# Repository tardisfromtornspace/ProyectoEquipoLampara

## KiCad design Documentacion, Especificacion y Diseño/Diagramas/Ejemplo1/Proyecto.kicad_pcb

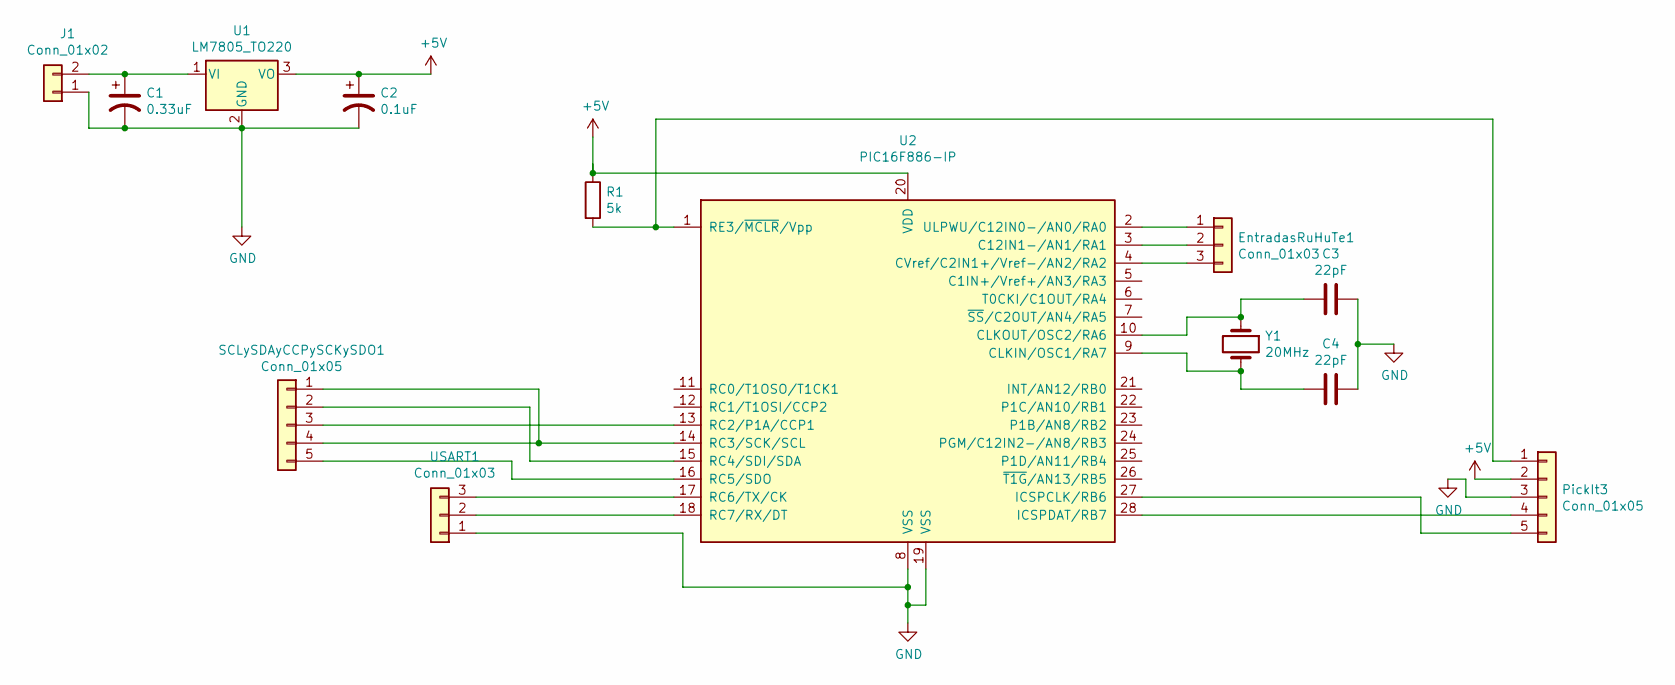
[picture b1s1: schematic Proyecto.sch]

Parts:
C1: 0.33uF; CP_Radial_D5.0mm_P2.50mm
C2: 0.1uF; CP_Radial_D5.0mm_P2.50mm
C3, C4: 22pF; C_Disc_D5.0mm_W2.5mm_P2.50mm
EntradasRuHuTe1: Conn_01x03; PinHeader_1x03_P2.54mm_Vertical
J1: Conn_01x02; TerminalBlock_bornier-2_P5.08mm
PickIt3: Conn_01x05; PinHeader_1x05_P2.54mm_Vertical
R1: 5k; R_Axial_DIN0204_L3.6mm_D1.6mm_P7.62mm_Horizontal
SCLySDAyCCPySCKySDO1: Conn_01x05; PinHeader_1x05_P2.54mm_Vertical
U1: LM7805_TO220; TO-220-3_Vertical
U2: PIC16F886-IP; DIP-28_W7.62mm_LongPads
USART1: Conn_01x03; PinHeader_1x03_P2.54mm_Vertical
Y1: 20MHz; Crystal_HC18-U_Vertical

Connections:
+5V: C2.1, PickIt3.2, R1.1, U1.3 (VO), U2.20 (VDD)
GND: C1.2, C2.2, C3.1, C4.1, J1.1, PickIt3.3, U1.2 (GND), U2.8 (VSS), U2.19 (VSS), USART1.1
unnamed: C1.1, J1.2, U1.1 (VI)
unnamed: C3.2, U2.10 (CLKOUT/OSC2/RA6), Y1.1
unnamed: C4.2, U2.9 (CLKIN/OSC1/RA7), Y1.2
unnamed: EntradasRuHuTe1.1, U2.2 (ULPWU/C12IN0-/AN0/RA0)
unnamed: EntradasRuHuTe1.2, U2.3 (C12IN1-/AN1/RA1)
unnamed: EntradasRuHuTe1.3, U2.4 (CVref/C2IN1+/Vref-/AN2/RA2)
unnamed: PickIt3.1, R1.2, U2.1 (RE3/~MCLR~/Vpp)
unnamed: PickIt3.4, U2.28 (ICSPDAT/RB7)
unnamed: PickIt3.5, U2.27 (ICSPCLK/RB6)
unnamed: SCLySDAyCCPySCKySDO1.1, SCLySDAyCCPySCKySDO1.4, U2.14 (RC3/SCK/SCL)
unnamed: SCLySDAyCCPySCKySDO1.2, U2.15 (RC4/SDI/SDA)
unnamed: SCLySDAyCCPySCKySDO1.3, U2.13 (RC2/P1A/CCP1)
unnamed: SCLySDAyCCPySCKySDO1.5, U2.16 (RC5/SDO)
unnamed: U2.17 (RC6/TX/CK), USART1.3
unnamed: U2.18 (RC7/RX/DT), USART1.2

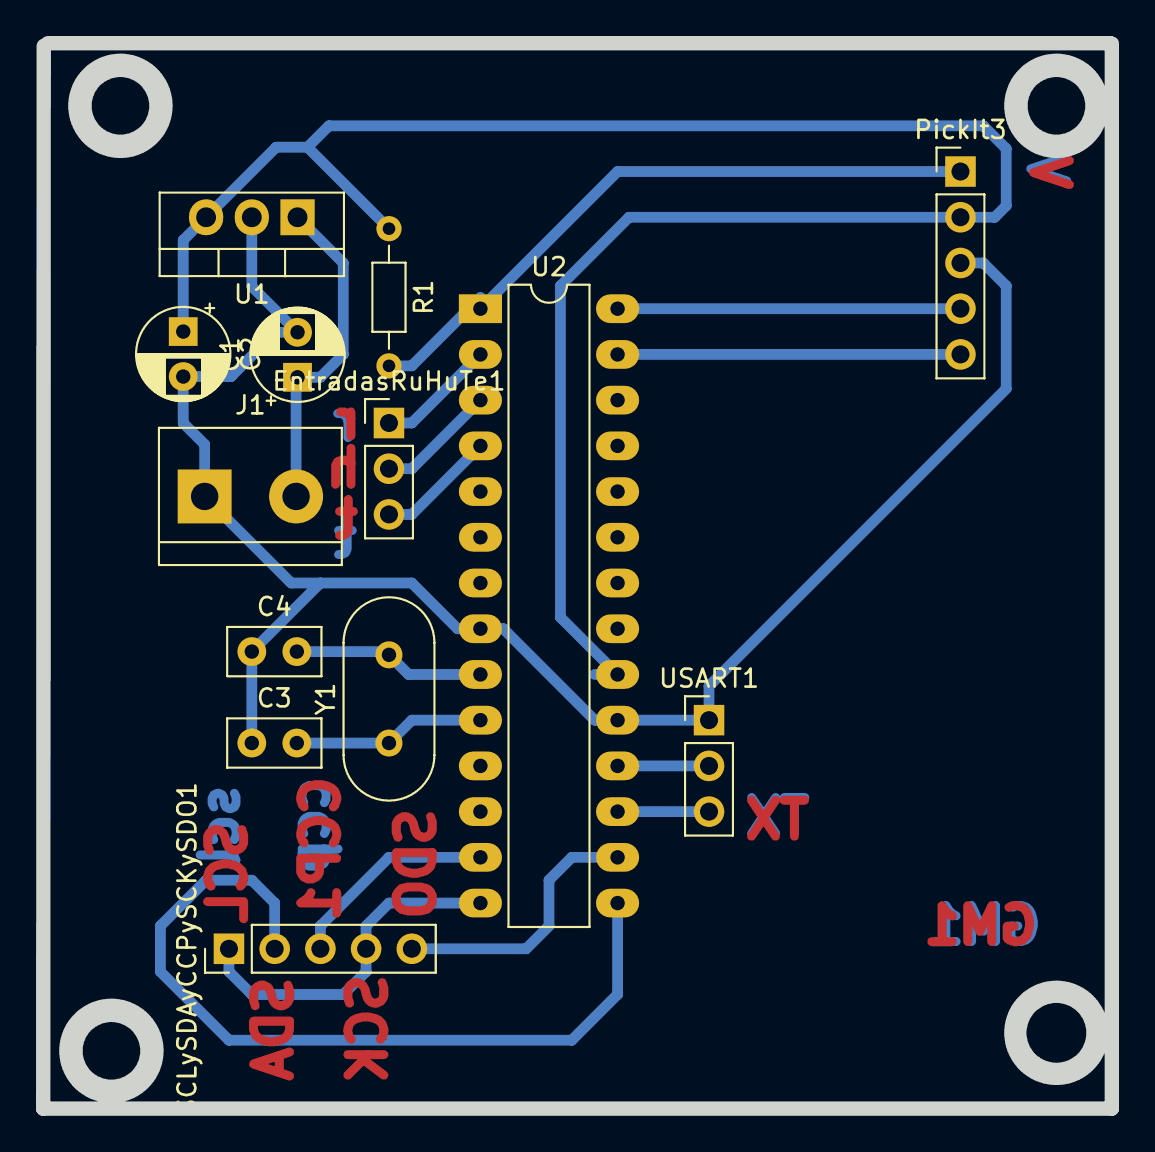
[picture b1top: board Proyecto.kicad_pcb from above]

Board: 2 copper layers, 59.4 x 59.2 mm, 13 parts (0 on the bottom side), 17 nets.

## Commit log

2022-10-16 Primer file
    ss
2022-10-16 Aniadida documentacion mñinima
2022-10-16 Actualizado PWM y adc un poco
2022-10-20 Aniadias cosas del proyecto
2022-10-21 Ampliado un poco diagrama de bloques
2022-10-21 Ampliado un poco diagrama de bloques aniadiendo un actor limux
2022-10-23 Sesión semana 1 - se compeltará lo de hoy mañana
2022-10-23 Actualizado documentación un poco, mañana completamos lo que dijimos de diagramas de bloques y estados y las trazas, además de la parte documentacion HW y SW
2022-10-24 Aniadidas algunas cosillas
2022-10-24 Compeltado diagrama SW a alto nivel y parte de trazas, mañana compeltamos el diagrama de SW a bajo nivel de estados y su documento respectivo
2022-10-24 mañana necesitamos completar las trazas aún mejor para componentes HW, el diagrama de SW a bajo nivel de estados y su documento respectivo
2022-10-25 Diag estados inicial a refinar, actualizacion documento disenioHW y SW
2022-10-25 Completados diseño SW y empezadas trazas y documentacion HWSw
2022-10-25 Removidos archivos temporales
2022-10-27 Actualizados precios con el LED
2022-10-27 DIseño logico parte 1 y refinamiento de precios
2022-10-29 Sesión del 29 de octubre de 2022
2022-10-30 Domingo 30 de Octubre 2022, discusiones sobre programación del software SMA__COMP en Linux, si usar el SW de clase de miniterm u otros, se clarificará en la próxima sesión de clase
2022-10-30 Actualziados tiempos de Ismael
2022-11-03 Tratado de hacer parte del circuito sin cruces y con especificaciones
2022-11-03 Idme diciendo que os parece
2022-11-03 Arreglada pequeña errata en el Word
2022-11-04 arreglo del circuito y documento, disenio fisico y video arq alto nivel completados
2022-11-07 Diagrama de Estados adicional completado, actualizada documentación, haremos el vídeo el miércoles
2022-11-09 Sesion de 9 de noviembre 2022
2022-11-10 Arreglados algunos comentarios en los diagramas, finalizado documentación HW y SW a nivel 1, actualizadas incidencias, creando más código del programa final
2022-11-11 Añadido trabajo isma y alex
2022-11-15 aniadidos tiempos de sma-comp adicionales
2022-11-17 Actualización de documentación y del programa - seguiré haciendo la parte SW de SMA_LAMP cuando pueda
2022-11-18 Refinado el código a algo con más sentido
2022-11-22 Pruebas comunes entre SMA_LAMP y SMA_COMP
2022-11-22 Pruebas comunes entre SMA_LAMP y SMA_COMP v2
2022-11-22 Caso de pruebas a nivel teórico completado
2022-11-23 Actualizado el documento de pruebas un poco
2022-11-23 Ampliado documento de pruebas un poco más
2022-11-24 Disenio pruebas video
2022-11-25 Arreglos al main.c del i2c
2022-12-01 Arreglos en código y cosas del protocolo de pruebas
2022-12-07 Documento de especificación y disenio final
2022-12-15 Algunos videos de pruebas y programa main ajustado algo para resolver sw
2022-12-22 Actualizados algunos documentos
2022-12-22 Entrega 2
2023-01-06 mejora ligera de la entrega
